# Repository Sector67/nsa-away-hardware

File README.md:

nsa-away-hardware
=================

Random number generator that fills out two SD cards, dumps to a HID keyboard, or decrypts data.

<h2>Block diagram</h2>
<ul>
<li>LCD - displays progress, function</li>
<li>Microcontroller - writes to USB/SD</li>
<li>SD card slots (2)</li>
<li>USB - optional output</li>
<li>switch - on/off</li>
<li>two buttons (mode and start)
<ul>
	<li>create SD clones</li>
	<li>copy SD card</li>
	<li>random->usb keyboard</li>
	<li>usb keyboard</li>
</ul></li>
<li>RNG * 8</li>
<li>Power supply: battery or USB</li>
</ul>

<h2>Purpose</h2>

There are 6 possible uses for this device:

<ol>
<li>Create two identical SD cards that contain the same OTP with the same random data. These SD cards are then distributed to the two people who need to communicate, and they have a source of secure shared random data.</li>
<li>Copy an SD card. If an OTP needs to be transferred to a third party, or the second party loses their key, this device can clone an existing SD card.</li>
<li>Random number generator over USB. It is sometimes necessary to have a random number generator for other purposes. This generates random data and pipes it out over USB as an HID keyboard. It does this so that it won't allow traffic IN to the machine, potentially compromising it.</li>
<li>USB Keyboard for translating. When a message is sent, the user needs to be able to encrypt or decrypt it. This allows the user to plug in the device and consume the random data from the OTP.</li>
<li>In a pinch, the device could be used to decrypt when a USB connection isn't available. In this mode, the user specifies the offset and starts reading characters, which are displayed one by one. Time consuming, but it works.</li>
<li>Serial port to keyboard. In this mode, anything spit out over the USB serial port (FTDI) gets printed to the keyboard. This allows you to connect a secure device to an unsecure device without the need for drivers and without exposing the secure device.</li>
</ol>
<h2>Theory of operation</h2>

The device uses two transistors with their bases touching to create avalance noise. This noise is amplified and sent to a multiplexor. 8 of these noise circuits together are used to generate a byte of data. The data is then de-biased and whitened, and passed appropriately depending on the mode.

<h2>Security</h2>

There are a few potential vectors for attack. The first and most obvious is to compromise the microcontroller. It is our belief that in large volumes a custom IC could be designed to prevent this from happening. In the short term, we can burn the fuses on the microcontroller to prevent it from being overwritten.

<h2>UI</h2>

A simple LCD based on an HD44780 is sufficient. This display would allow the user to change modes, and could possibly be used to read and translate data in a pinch.

Back button allows the user to go to a previous screen.

<h3>Home Screen</h3>
<ul>
<li>Shows if the battery is charging and what its status is.</li>
<li>Up/Down arrows let the user choose between modes. If no USB is detected, then it will not show USB-required modes.</li>
<li>Enter button to go into a mode.</li>
</ul>

<h3>Create SD Clones</h3>
<ul>
<li>Up/Down to select data size</li>
<li>Enter button to start. Doesn't start immediately but rather asks to verify that both cards will be erased and won't work in computers.</li>
<li>While running, shows % complete, Enter button to stop.</li>
<li>When complete, says "complete."</li>
</ul>

<h3>Copy SD card</h3>
<ul>
<li>Always copies from one side to the other. No option to swap (too confusing and dangerous).</li>
<li>Enter to start. Doesn't start immediately but rather asks the user to verify the original is in the correct slot.</li>
<li>Enter again to start.</li>
<li>Once complete, says "Complete".</li>
</ul>

<h3>Random->USB Keyboard</h3>
<ul>
<li>Up/Down arrows to select amount (stream, 1 byte, 8 bytes, 256 bytes, 1kb, 512kb, 1mb, 10mb, 128mb, 1gb.)</li>
<li>Enter to have it spit out that much. % complete to show progress.</li>
<li>Back to prematurely cancel.</li>
</ul>

<h3>SD->USB Keyboard</h3>
<ul>
<li>Up/Down/Enter to select each digit of the offset. Enter on Blank to complete offset.</li>
<li>Every enter pressed thereafter shows offset and in parentheses character count for that session and the character for that offset.</li>
<li>Every passed character gets zeroed out on the SD card so that it is lost forever.</li>
<li>Back to escape to the home screen.</li>
</ul>

<h3>SD->Display</h3>
<ul>
<li>Same as SD->USB Keyboard, except that it doesn't try to pump the result out over USB. Just for the display.</li>
</ul>

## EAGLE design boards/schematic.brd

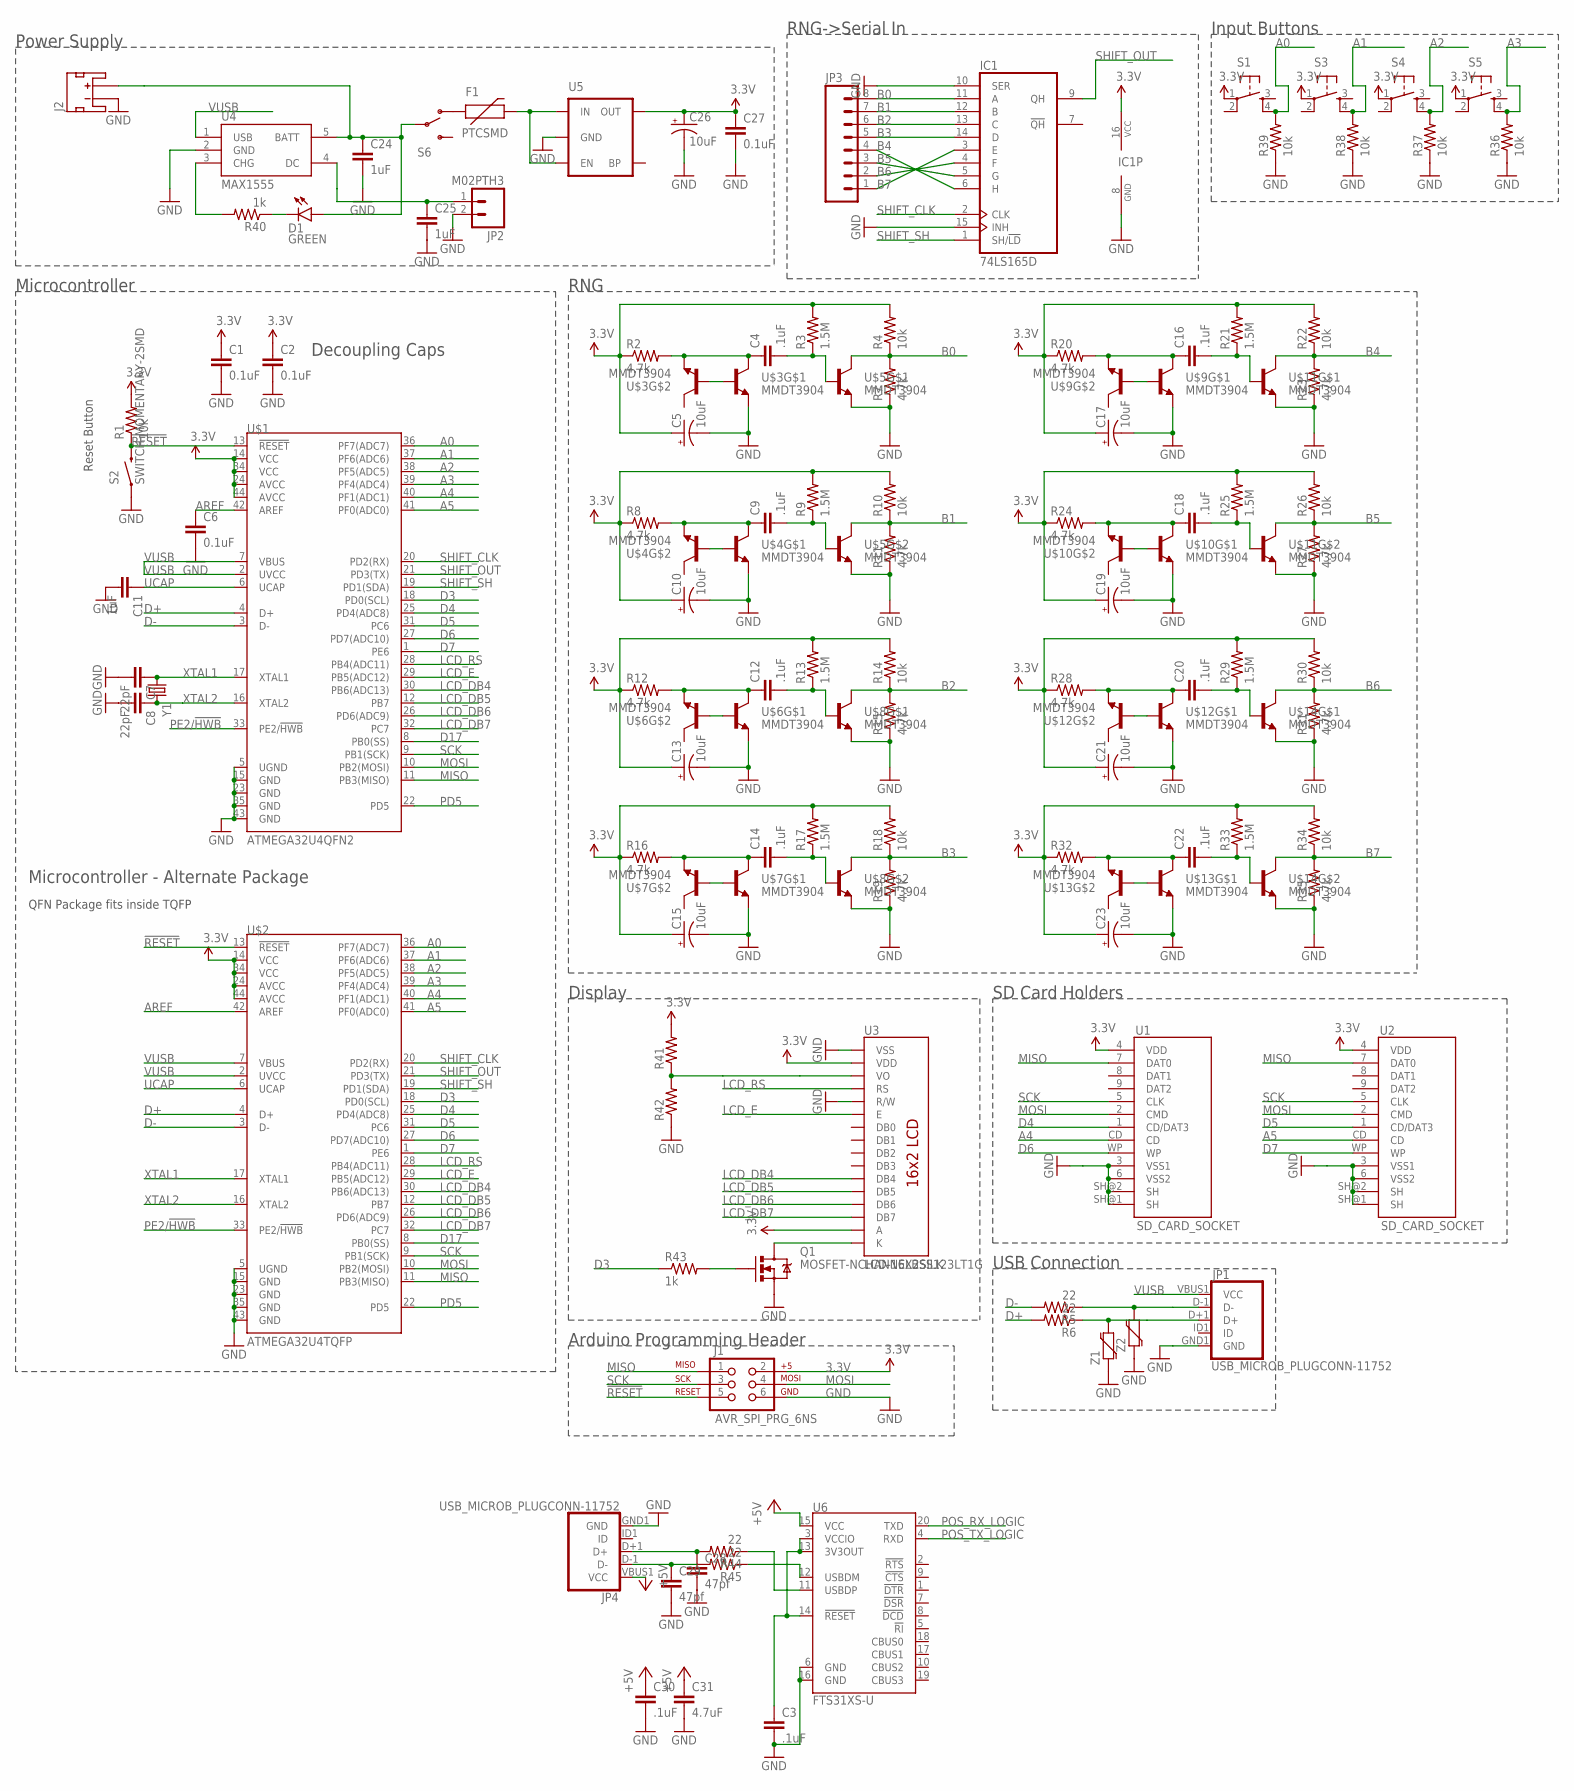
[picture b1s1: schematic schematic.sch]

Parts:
C1, C2, C6, C27: 0.1uF; 0603-CAP
C3, C4, C9, C12, C14, C16, C18, C20, C22, C30: .1uF; 0603-CAP
C5, C10, C13, C15, C17, C19, C21, C23, C26: 10uF; EIA3216
C7, C8: 22pF; 0603-CAP
C11, C24, C25: 1uF; 0603-CAP
C28, C29: 47pf; 0603-CAP
C31: 4.7uF; 0603-CAP
D1: GREEN; LED-0603
F1: PTCSMD; PTC-1206
IC1: 74LS165D; SO16
J1: AVR_SPI_PRG_6NS; 2X3-NS
J2: JST_2MM_MALE; JST-2-SMD
JP1, JP4: USB_MICROB_PLUGCONN-11752; USB-B-MICRO-SMD_V03
JP2: M02PTH3; 1X02_LONGPADS
JP3: M081X08; 1X08
Q1: MOSFET-NCHANNELBSS123LT1G; SOT23
R1, R4, R10, R14, R18, R22, R26, R30, R34, R36, R37, R38, R39: 10k; 0603-RES
R2, R7, R8, R11, R12, R15, R16, R19, R20, R23, R24, R27, R28, R31, R32, R35: 4.7k; 0603-RES
R3, R9, R13, R17, R21, R25, R29, R33: 1.5M; 0603-RES
R5, R6, R44, R45: 22; 0603-RES
R40, R43: 1k; 0603-RES
R41, R42: RESISTOR0603-RES; 0603-RES
S1, S3, S4, S5: TAC_SWITCHPTH; TACTILE-PTH
S2: SWITCH-MOMENTARY-2SMD; TACTILE-SWITCH-SMD
S6: SWITCH-SPDTPTH; SWITCH-SPDT
U1, U2: SD_CARD_SOCKET; SD_1:1
U3: LCD-16X2SILK; LCD-16X2
U4: MAX1555; SOT23-5
U5: MIC52053.3V; SOT23-5
U6: FTS31XS-U; SSOP20_L
U$1: ATMEGA32U4QFN2; SPARKFUN-DIGITALIC_QFN-44-NOPAD
U$2: ATMEGA32U4TQFP; SPARKFUN-DIGITALIC_TQFP44
U$3, U$4, U$5, U$6, U$7, U$8, U$9, U$10, U$11, U$12, U$13, U$14: MMDT3904; SOT363
Y1: CRYSTALSMD; HC49UP
Z1, Z2: VARISTOR-0603; 0603-RES

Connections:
3.3V: C1.1, C2.1, C5.A (+), C10.A (+), C13.A (+), C15.A (+), C17.A (+), C19.A (+), C21.A (+), C23.A (+), C26.A (+), C27.1, IC1.16 (VCC), J1.2, R1.2, R2.1, R3.2, R4.2, R8.1, R9.2, R10.2, R12.1, R13.2, R14.2, R16.1, R17.2, R18.2, R20.1, R21.2, R22.2, R24.1, R25.2, R26.2, R28.1, R29.2, R30.2, R32.1, R33.2, R34.2, R41.2, S1.1, S3.1, S4.1, S5.1, U1.4 (VDD), U2.4 (VDD), U3.2 (VDD), U3.15 (A), U5.5 (OUT), U$1.14 (VCC), U$1.24 (AVCC), U$1.34 (VCC), U$1.44 (AVCC), U$2.14 (VCC), U$2.24 (AVCC), U$2.34 (VCC), U$2.44 (AVCC)
!RESET: J1.5, R1.1, S2.3 (2), U$1.13 (!RESET), U$2.13 (!RESET)
+5V: C30.1, C31.1, JP4.VBUS1 (VCC), U6.15 (VCC)
A0: R39.2, S1.4, U$1.36 (PF7(ADC7)), U$2.36 (PF7(ADC7))
A1: R38.2, S3.4, U$1.37 (PF6(ADC6)), U$2.37 (PF6(ADC6))
A2: R37.2, S4.4, U$1.38 (PF5(ADC5)), U$2.38 (PF5(ADC5))
A3: R36.2, S5.4, U$1.39 (PF4(ADC4)), U$2.39 (PF4(ADC4))
A4: U1.CD, U$1.40 (PF1(ADC1)), U$2.40 (PF1(ADC1))
A5: U2.CD, U$1.41 (PF0(ADC0)), U$2.41 (PF0(ADC0))
AREF: C6.1, U$1.42 (AREF), U$2.42 (AREF)
B0: IC1.11 (A), JP3.8, R4.1, R7.2, U$5.6 (C)
B1: IC1.12 (B), JP3.7, R10.1, R11.2, U$5.3 (C)
B2: IC1.13 (C), JP3.6, R14.1, R15.2, U$8.6 (C)
B3: IC1.14 (D), JP3.5, R18.1, R19.2, U$8.3 (C)
B4: IC1.3 (E), JP3.1, R22.1, R23.2, U$11.6 (C)
B5: IC1.4 (F), JP3.2, R26.1, R27.2, U$11.3 (C)
B6: IC1.5 (G), JP3.3, R30.1, R31.2, U$14.6 (C)
B7: IC1.6 (H), JP3.4, R34.1, R35.2, U$14.3 (C)
D3: R43.1, U$1.18 (PD0(SCL)), U$2.18 (PD0(SCL))
D4: U1.1 (CD/DAT3), U$1.25 (PD4(ADC8)), U$2.25 (PD4(ADC8))
D5: U2.1 (CD/DAT3), U$1.31 (PC6), U$2.31 (PC6)
D6: U1.WP, U$1.27 (PD7(ADC10)), U$2.27 (PD7(ADC10))
D7: U2.WP, U$1.1 (PE6), U$2.1 (PE6)
D17: U$1.8 (PB0(SS)), U$2.8 (PB0(SS))
D+: R6.2, U$1.4 (D+), U$2.4 (D+)
D-: R5.2, U$1.3 (D-), U$2.3 (D-)
GND: C1.2, C2.2, C3.2, C5.C (-), C6.2, C7.2, C8.2, C10.C (-), C11.2, C13.C (-), C15.C (-), C17.C (-), C19.C (-), C21.C (-), C23.C (-), C24.2, C25.2, C26.C (-), C27.2, C28.2, C29.2, C30.2, C31.2, IC1.8 (GND), IC1.10 (SER), IC1.15 (INH), J1.6, J2.1 (-), JP1.GND1 (GND), JP2.2, JP4.GND1 (GND), Q1.2 (S), R7.1, R11.1, R15.1, R19.1, R23.1, R27.1, R31.1, R35.1, R36.1, R37.1, R38.1, R39.1, R42.1, S2.1, U1.3 (VSS1), U1.6 (VSS2), U1.SH@1 (SH), U1.SH@2 (SH), U2.3 (VSS1), U2.6 (VSS2), U2.SH@1 (SH), U2.SH@2 (SH), U3.1 (VSS), U3.5 (R/W), U4.2 (GND), U5.2 (GND), U6.6 (GND), U6.16 (GND), U$1.5 (UGND), U$1.15 (GND), U$1.23 (GND), U$1.35 (GND), U$1.43 (GND), U$2.5 (UGND), U$2.15 (GND), U$2.23 (GND), U$2.35 (GND), U$2.43 (GND), U$3.1 (E), U$4.1 (E), U$5.1 (E), U$5.4 (E), U$6.1 (E), U$7.1 (E), U$8.1 (E), U$8.4 (E), U$9.1 (E), U$10.1 (E), U$11.1 (E), U$11.4 (E), U$12.1 (E), U$13.1 (E), U$14.1 (E), U$14.4 (E), Z1.1, Z2.1
LCD_DB4: U3.11 (DB4), U$1.30 (PB6(ADC13)), U$2.30 (PB6(ADC13))
LCD_DB5: U3.12 (DB5), U$1.12 (PB7), U$2.12 (PB7)
LCD_DB6: U3.13 (DB6), U$1.26 (PD6(ADC9)), U$2.26 (PD6(ADC9))
LCD_DB7: U3.14 (DB7), U$1.32 (PC7), U$2.32 (PC7)
LCD_E: U3.6 (E), U$1.29 (PB5(ADC12)), U$2.29 (PB5(ADC12))
LCD_RS: U3.4 (RS), U$1.28 (PB4(ADC11)), U$2.28 (PB4(ADC11))
MISO: J1.1, U1.7 (DAT0), U2.7 (DAT0), U$1.11 (PB3(MISO)), U$2.11 (PB3(MISO))
MOSI: J1.4, U1.2 (CMD), U2.2 (CMD), U$1.10 (PB2(MOSI)), U$2.10 (PB2(MOSI))
unnamed: U$3.2 (B), U$3.5 (B)
unnamed: C4.1, R2.2, U$3.4 (E), U$3.6 (C)
unnamed: C24.1, D1.A, J2.2 (+), S6.2, U4.5 (BATT)
unnamed: C4.2, R3.1, U$5.2 (B)
unnamed: U$4.2 (B), U$4.5 (B)
unnamed: C9.1, R8.2, U$4.4 (E), U$4.6 (C)
unnamed: C9.2, R9.1, U$5.5 (B)
unnamed: C25.1, JP2.1, U4.4 (DC)
unnamed: U$6.2 (B), U$6.5 (B)
unnamed: C12.1, R12.2, U$6.4 (E), U$6.6 (C)
unnamed: C12.2, R13.1, U$8.2 (B)
unnamed: F1.1, S6.1 (O)
unnamed: U$7.2 (B), U$7.5 (B)
unnamed: C14.1, R16.2, U$7.4 (E), U$7.6 (C)
unnamed: C14.2, R17.1, U$8.5 (B)
unnamed: R40.2, U4.3 (CHG)
unnamed: U$9.2 (B), U$9.5 (B)
unnamed: C16.1, R20.2, U$9.4 (E), U$9.6 (C)
unnamed: C16.2, R21.1, U$11.2 (B)
unnamed: D1.C, R40.1
unnamed: Q1.1 (G), R43.2
unnamed: C28.1, JP4.D+1 (D+), R44.2
unnamed: C29.1, JP4.D-1 (D-), R45.2
unnamed: U$10.2 (B), U$10.5 (B)
unnamed: C18.1, R24.2, U$10.4 (E), U$10.6 (C)
unnamed: JP1.D-1 (D-), R5.1, Z2.2
unnamed: JP1.D+1 (D+), R6.1, Z1.2
unnamed: C18.2, R25.1, U$11.5 (B)
unnamed: Q1.3 (D), U3.16 (K)
unnamed: U$12.2 (B), U$12.5 (B)
unnamed: C20.1, R28.2, U$12.4 (E), U$12.6 (C)
unnamed: C20.2, R29.1, U$14.2 (B)
unnamed: F1.2, U5.1 (IN), U5.3 (EN)
unnamed: U$13.2 (B), U$13.5 (B)
unnamed: C22.1, R32.2, U$13.4 (E), U$13.6 (C)
unnamed: C22.2, R33.1, U$14.5 (B)
unnamed: R44.1, U6.11 (USBDP)
unnamed: R45.1, U6.12 (USBDM)
unnamed: R41.1, R42.2, U3.3 (VO)
unnamed: C3.1, U6.3 (VCCIO), U6.13 (3V3OUT), U6.14 (!RESET)
PD5: U$1.22 (PD5), U$2.22 (PD5)
PE2/!HWB: U$1.33 (PE2/!HWB), U$2.33 (PE2/!HWB)
POS_RX_LOGIC: U6.20 (TXD)
POS_TX_LOGIC: U6.4 (RXD)
SCK: J1.3, U1.5 (CLK), U2.5 (CLK), U$1.9 (PB1(SCK)), U$2.9 (PB1(SCK))
SHIFT_CLK: IC1.2 (CLK), U$1.20 (PD2(RX)), U$2.20 (PD2(RX))
SHIFT_OUT: IC1.9 (QH), U$1.21 (PD3(TX)), U$2.21 (PD3(TX))
SHIFT_SH: IC1.1 (SH/!LD), U$1.19 (PD1(SDA)), U$2.19 (PD1(SDA))
UCAP: C11.1, U$1.6 (UCAP), U$2.6 (UCAP)
VUSB: JP1.VBUS1 (VCC), U4.1 (USB), U$1.2 (UVCC), U$1.7 (VBUS), U$2.2 (UVCC), U$2.7 (VBUS)
XTAL1: C7.1, U$1.17 (XTAL1), U$2.17 (XTAL1), Y1.1
XTAL2: C8.1, U$1.16 (XTAL2), U$2.16 (XTAL2), Y1.2

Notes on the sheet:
Microcontroller
Decoupling Caps
USB Connection
Arduino Programming Header
Power Supply
Microcontroller - Alternate Package
RNG
SD Card Holders
RNG->Serial In
Display
Input Buttons
Reset Button
QFN Package fits inside TQFP

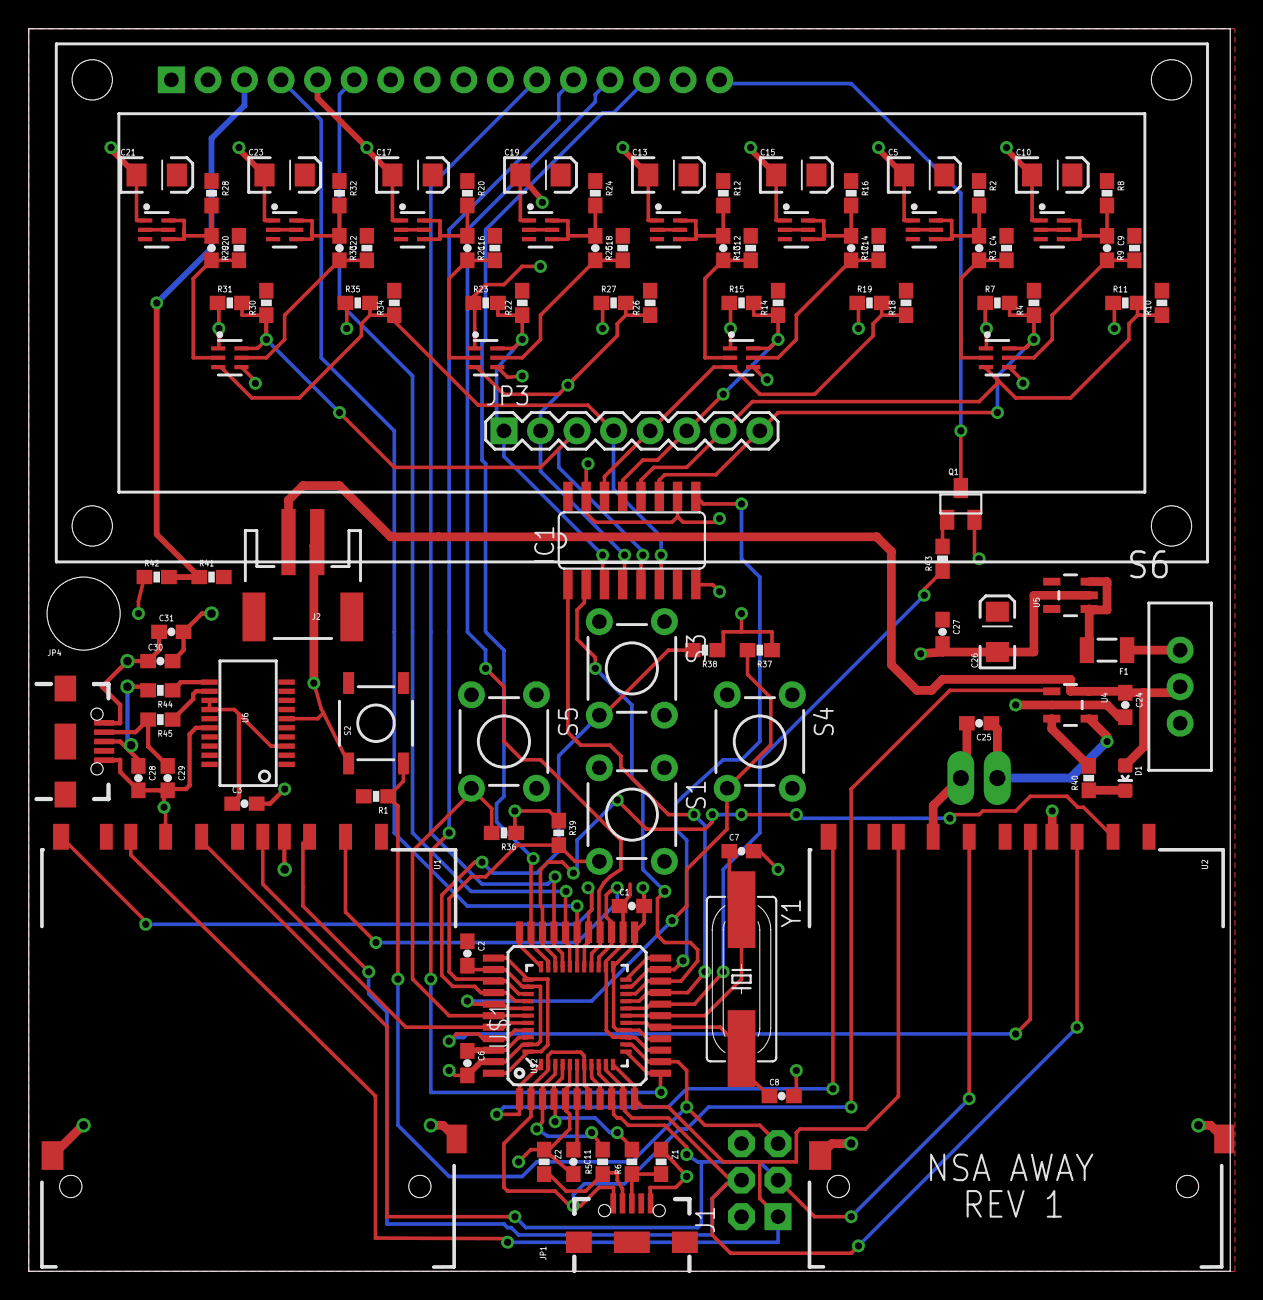
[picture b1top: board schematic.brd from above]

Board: 2 copper layers, 83.5 x 86.3 mm, 115 parts (0 on the bottom side), 85 nets.

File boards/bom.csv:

"Qty";"Value";"Device";"Package";"Parts";"Description";"PROD_ID";"VALUE";
"1";"";"CRYSTALSMD";"HC49UP";"Y1";"Various standard crystals. Proven footprints. Spark Fun Electronics SKU : COM-00534";"";"";
"1";"";"JST_2MM_MALE";"JST-2-SMD";"J2";"Mates to single-cell LiPo batteries.";"CONN-08352";"";
"1";"";"M081X08";"1X08";"JP3";"Header 8";"";"";
"1";"";"MIC52053.3V";"SOT23-5";"U5";"MIC5205 150mA vreg";"VREG-00822";"";
"2";"";"RESISTOR0603-RES";"0603-RES";"R41, R42";"Resistor";"";"";
"1";"";"SWITCH-SPDTPTH";"SWITCH-SPDT";"S6";"SPDT Switch";"";"";
"4";"";"TAC_SWITCHPTH";"TACTILE-PTH";"S1, S3, S4, S5";"Momentary Switch";"";"";
"2";"";"VARISTOR-0603";"0603-RES";"Z1, Z2";"Varistor";"";"";
"8";".1uF";"CAP0603-CAP";"0603-CAP";"C4, C9, C12, C14, C16, C18, C20, C22";"Capacitor";"";"";
"4";"0.1uF";"CAP0603-CAP";"0603-CAP";"C1, C2, C6, C27";"Capacitor";"";"";
"8";"1.5M";"RESISTOR0603-RES";"0603-RES";"R3, R9, R13, R17, R21, R25, R29, R33";"Resistor";"";"";
"13";"10k";"RESISTOR0603-RES";"0603-RES";"R1, R4, R10, R14, R18, R22, R26, R30, R34, R36, R37, R38, R39";"Resistor";"";"";
"9";"10uF";"CAP_POL1206";"EIA3216";"C5, C10, C13, C15, C17, C19, C21, C23, C26";"Capacitor Polarized";"";"";
"2";"1k";"RESISTOR0603-RES";"0603-RES";"R40, R43";"Resistor";"";"";
"3";"1uF";"CAP0603-CAP";"0603-CAP";"C11, C24, C25";"Capacitor";"";"";
"2";"22";"RESISTOR0603-RES";"0603-RES";"R5, R6";"Resistor";"";"";
"2";"22pF";"CAP0603-CAP";"0603-CAP";"C7, C8";"Capacitor";"";"";
"16";"4.7k";"RESISTOR0603-RES";"0603-RES";"R2, R7, R8, R11, R12, R15, R16, R19, R20, R23, R24, R27, R28, R31, R32, R35";"Resistor";"";"";
"1";"74LS165D";"74LS165D";"SO16";"IC1";"8-bit parallel load SHIFT REGISTER";"";"";
"1";"ATMEGA32U4QFN2";"ATMEGA32U4QFN2";"SPARKFUN-DIGITALIC_QFN-44-NOPAD";"U$1";"Atmel 44-pin 8-bit Microcontroller with 32KBytes of ISP Flash and USB Controller -----";"";"";
"1";"ATMEGA32U4TQFP";"ATMEGA32U4TQFP";"SPARKFUN-DIGITALIC_TQFP44";"U$2";"Atmel 44-pin 8-bit Microcontroller with 32KBytes of ISP Flash and USB Controller -----";"IC-11161";"";
"1";"AVR_SPI_PRG_6NS";"AVR_SPI_PRG_6NS";"2X3-NS";"J1";"AVR ISP 6 Pin";"";"";
"1";"GREEN";"LED-GREEN0603";"LED-0603";"D1";"Various green LEDs";"DIO-00821";"GREEN";
"1";"LCD-16X2SILK";"LCD-16X2SILK";"LCD-16X2";"U3";"Standard text-only 16x2 parallel input LCD";"";"";
"1";"M02PTH3";"M02PTH3";"1X02_LONGPADS";"JP2";"Standard 2-pin 0.1" header. Use with";"";"";
"1";"MAX1555";"MAX1555";"SOT23-5";"U4";"MAX1555 Lithium Charger IC";"";"";
"12";"MMDT3904";"TRANSISTOR_NPN2UPMMDT3904";"SOT363";"U$3, U$4, U$5, U$6, U$7, U$8, U$9, U$10, U$11, U$12, U$13, U$14";"2-up package of NPN transistors";"TRANS-09373";"MMDT3904";
"1";"MOSFET-NCHANNELBSS123LT1G";"MOSFET-NCHANNELBSS123LT1G";"SOT23";"Q1";"Common NMOSFET Parts";"TRANS-08345";"";
"1";"PTCSMD";"PTCSMD";"PTC-1206";"F1";"Resettable Fuse PTC";"RES-11150";"";
"2";"SD_CARD_SOCKET";"SD_CARD_SOCKET";"SD_1:1";"U1, U2";"SD Memory Card Connector, push-push normal type, CD enable, WP enable";"";"";
"1";"SWITCH-MOMENTARY-2SMD";"SWITCH-MOMENTARY-2SMD";"TACTILE-SWITCH-SMD";"S2";"Various NO switches- pushbuttons, reed, etc";"";"";
"1";"USB_MICROB_PLUGCONN-11752";"USB_MICROB_PLUGCONN-11752";"USB-B-MICRO-SMD_V03";"JP1";"USB Micro-B connectors";"CONN-11752";"";

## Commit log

2014-07-06 Adding lots of content to the Readme
2014-07-06 Initial commits of the hardware, including complete schematic, layed out board, BOM, and PDF outputs of schematic and board.
2014-07-06 Adding the Rev number to the board.
2014-07-06 Update README.md
    Formatting for better display on github
2014-09-09 Adding a junction for clarity
    There was a junction missing from th schematic. Eagle showed the
    connection as being there, but the junction point was missing.
2014-09-09 Zipped gerbers of rev1 of the board sent off
2014-09-09 Adding the first go at the enclosure
2014-09-09 Adding firmware
    test sketches for the separate modules, with the NSA_AWAY sketch the
    intended final sketch for the project. It still has a ways to go with
    unimplemented features, but the groundwork is there.
2014-09-09 Courtesy period, delay between counter prints
2014-09-21 Various updates to main firmware app.
2014-09-21 lots of improvements
2014-09-21 New enclosure changes - easier to assemble, makes room for extra microusb, adds curves
2014-09-21 Adding curvy version of enclosure
2014-09-27 Improvements to the enclosure, tweaking the PCB
2014-09-29 Updates to the schematic, adding a PDF version for those who don't have Eagle.
2014-09-29 Lots of updates. Adds the serial passthrough.

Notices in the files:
parts and their libraries:
SparkFun-Connectors: Licensing: CC v3.0 Share-Alike You are welcome to use this library for commercial purposes.
SparkFun-Displays: Licensing: Creative Commons ShareAlike 4.0 International - https://creativecommons.org/licenses/by-sa/4.0
